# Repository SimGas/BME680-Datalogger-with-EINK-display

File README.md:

# BME680-Datalogger-with-EINK-display
Datalogger with BME680-Sensor, EINK Display, RTC and µSD-Storage

This project features a Arduino based datalogger reading temperature, relative humidity, pressure and IAQ values from a Bosch BME680 sensor. It displays the data at a 2.9 inch waveshare e-ink display using olikraus's u8g2 lib. The data is being synchronized with a DS3231 RTC and stored at a micro SD-Card.

The whole system runs on a adafruit feather M0 board

Please consider that this project is in a very early development status. I haven't completed the program code yet and I've just ordered the Mainboard.
If you want to make your own copy of this project, please contact me for information about recent unpublished changes.

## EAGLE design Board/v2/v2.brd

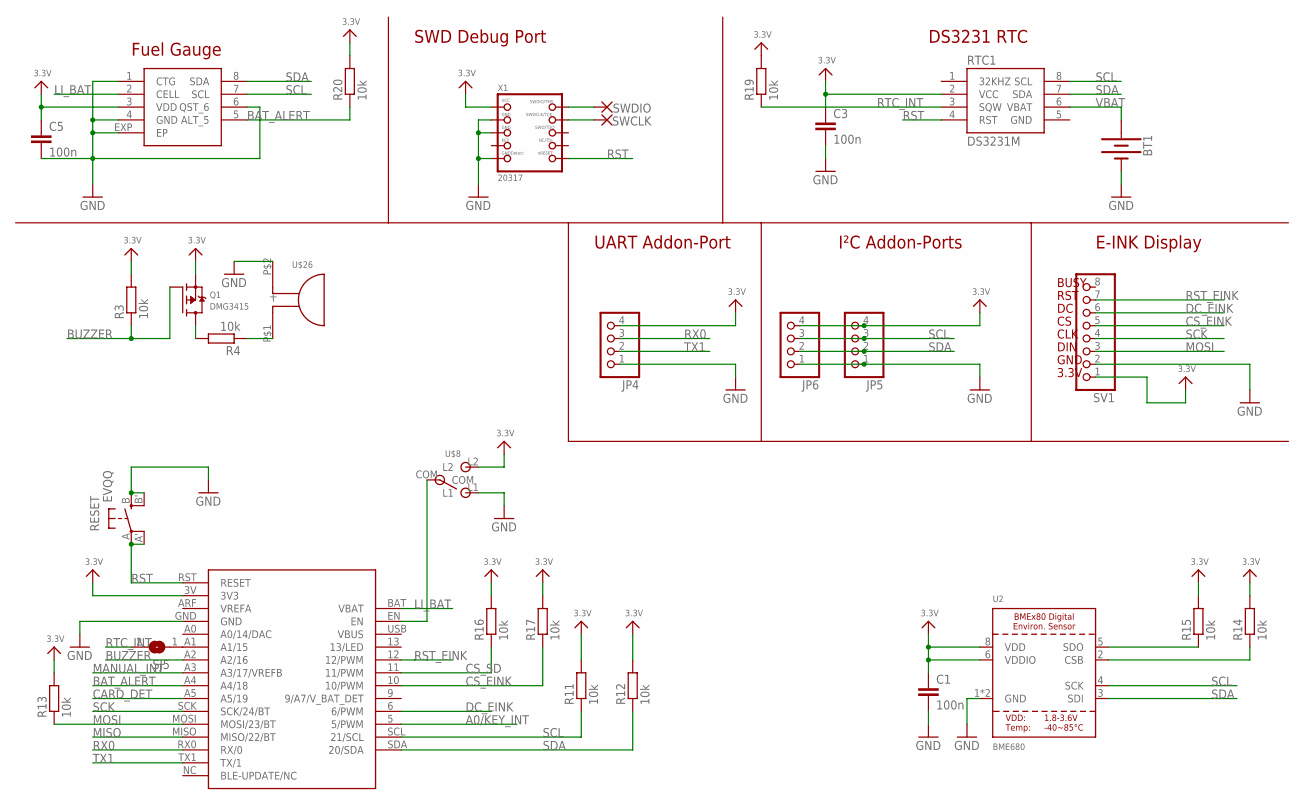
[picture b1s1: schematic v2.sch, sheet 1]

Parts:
BT1: BATTERY-12MM_SMD; BATTCON_12MM
C1, C3, C5: 100n; C0805
JP4, JP5, JP6: PINHD-1X04_2.54; 1X04
Q1: DMG3415; SOT23-WIDE
R3, R4, R11, R12, R13, R14, R15, R16, R17, R19, R20: 10k; R0805
RESET: EVQQ; EVQ-Q2
RTC1: DS3231M; SO08
SJ5: SOLDERJUMPERCLOSED; SOLDERJUMPER_CLOSEDWIRE
SV1: PINHD-1X08_2.54; 1X08
SWCLK: SMD1,27-2,54
SWDIO: SMD1,27-2,54
U2: BME680; BME280
U$8: MSK-12C02_SMD_SPDT_SWITCH; MSK-12C02
U$15: FEATHER_M0
U$26: DTS402G1; DET402G1
U$33: MAX17043; DFN-2X3
X1: 20317; 2X05_1.27MM_BOX_POSTS

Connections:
3.3V: C1.1, C3.1, C5.1, JP4.4, JP5.4, JP6.4, Q1.2 (S), R3.2, R11.2, R12.2, R13.2, R14.2, R15.2, R16.2, R17.2, R19.2, R20.2, RTC1.2 (VCC), SV1.1, U2.6 (VDDIO), U2.8 (VDD), U$8.L2, U$15.3V (3V3), U$33.3 (VDD), X1.1 (VCC); also elsewhere on the board
A0/KEY_INT: U$15.5 (5/PWM); also elsewhere on the board
BAT_ALERT: R20.1, U$15.A4 (A4/18), U$33.5 (ALT_5)
BUZZER: Q1.1 (G), R3.1, U$15.A2 (A2/16)
CARD_DET: U$15.A5 (A5/19); also elsewhere on the board
CS_EINK: R17.1, SV1.5, U$15.10 (10/PWM)
CS_SD: R16.1, U$15.11 (11/PWM); also elsewhere on the board
DC_EINK: SV1.6, U$15.6 (6/PWM)
EN: U$8.COM, U$15.EN
GND: BT1.GND (-), C1.2, C3.2, C5.2, JP4.1, JP5.1, JP6.1, RESET.B (S), RESET.B' (S1), RTC1.5 (GND), SV1.2, U2.1 (GND), U2.7 (GND), U$8.L1, U$15.GND, U$26.P$2 (-), U$33.1 (CTG), U$33.4 (GND), U$33.6 (QST_6), U$33.EXP (EP), X1.3 (GND), X1.5 (GND), X1.9 (GNDDETECT); also elsewhere on the board
LI_BAT: U$15.BAT (VBAT), U$33.2 (CELL)
MANUAL_INT: U$15.A3 (A3/17/VREFB); also elsewhere on the board
MISO: U$15.MISO (MISO/22/BT); also elsewhere on the board
MOSI: R13.1, SV1.3, U$15.MOSI (MOSI/23/BT); also elsewhere on the board
unnamed: R14.1, U2.2 (CSB)
unnamed: SJ5.1, U$15.A1 (A1/15)
unnamed: Q1.3 (D), R4.2
unnamed: R4.1, U$26.P$1 (+)
unnamed: R15.1, U2.5 (SDO)
unnamed: SWDIO.1, X1.2 (SWDIO)
unnamed: SWCLK.1, X1.4 (SWDCLK)
RST: RESET.A, RESET.A' (P1), RTC1.4 (RST), U$15.RST (RESET), X1.10 (NRESET)
RST_EINK: SV1.7, U$15.12 (12/PWM)
RTC_INT: R19.1, RTC1.3 (SQW), SJ5.2
RX0: JP4.3, U$15.RX0 (RX/0)
SCK: SV1.4, U$15.SCK (SCK/24/BT); also elsewhere on the board
SCL: JP5.3, JP6.3, R11.1, RTC1.8 (SCL), U2.4 (SCK), U$15.SCL (21/SCL), U$33.7 (SCL); also elsewhere on the board
SDA: JP5.2, JP6.2, R12.1, RTC1.7 (SDA), U2.3 (SDI), U$15.SDA (20/SDA), U$33.8 (SDA); also elsewhere on the board
TX1: JP4.2, U$15.TX1 (TX/1)
VBAT: BT1.PWR@1 (+), RTC1.6 (VBAT)

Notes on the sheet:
3.3V
GND
DIN
CLK
RST
BUSY
Fuel Gauge
SWD Debug Port
DS3231 RTC
E-INK Display
I²C Addon-Ports
UART Addon-Port

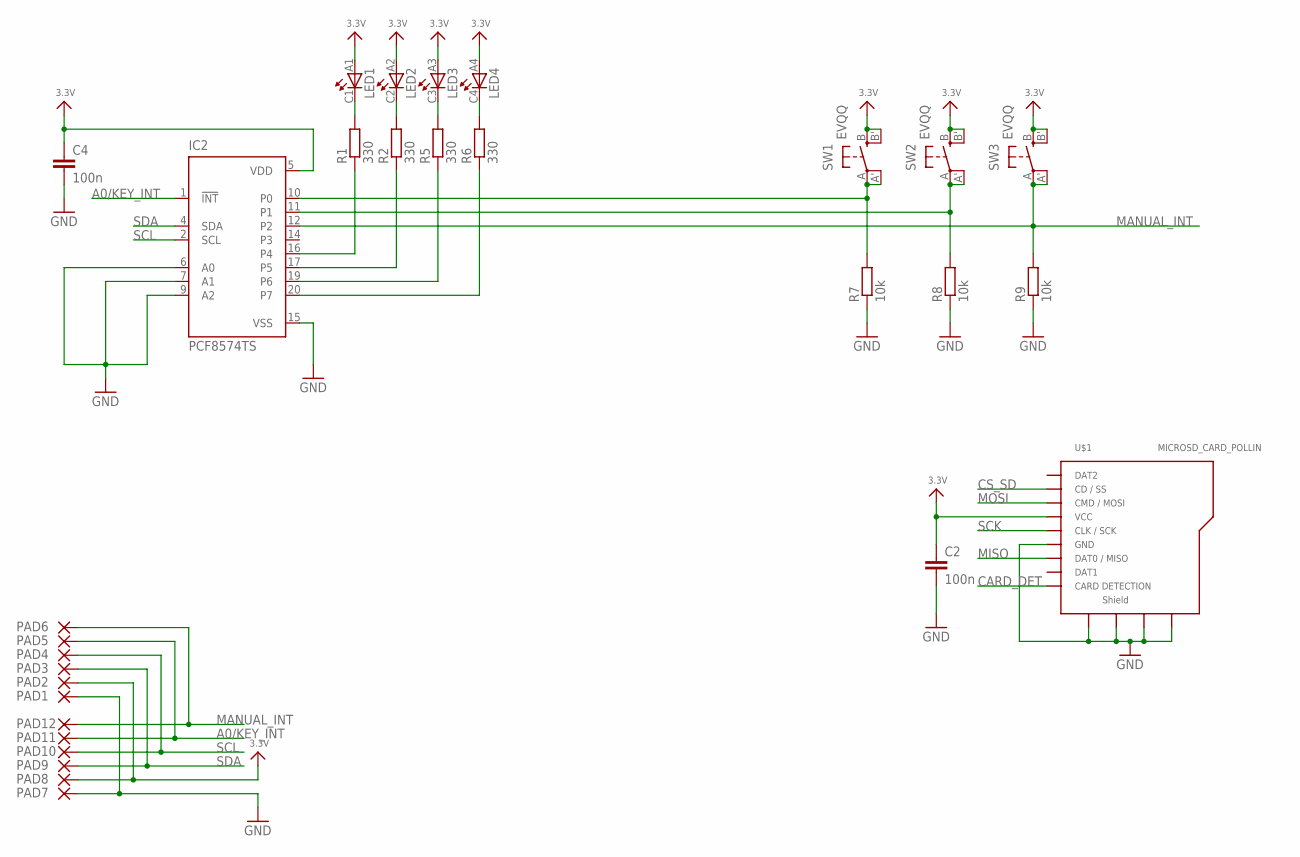
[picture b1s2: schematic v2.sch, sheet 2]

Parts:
C2, C4: 100n; C0805
IC2: PCF8574TS; SSOP20
PAD1, PAD2, PAD3, PAD4, PAD5, PAD6, PAD7, PAD8, PAD9, PAD10, PAD11, PAD12: SMD1,27-2,54
R1, R2, R5, R6: 330; R0805
R7, R8, R9: 10k; R0805
SW1, SW2, SW3: EVQQ; EVQ-Q2
U$1: MICROSD_CARD_POLLIN; MR**-AP*03**
U$5: LED_LIGHTGUIDE; LPA-C041301S-X

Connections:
3.3V: C2.1, C4.1, IC2.5 (VDD), PAD2.1, PAD8.1, SW1.B (S), SW1.B' (S1), SW2.B (S), SW2.B' (S1), SW3.B (S), SW3.B' (S1), U$1.VCC, U$5.A1, U$5.A2, U$5.A3, U$5.A4; also elsewhere on the board
A0/KEY_INT: IC2.1 (!INT), PAD5.1, PAD11.1; also elsewhere on the board
CARD_DET: U$1.CARD_DETECTION (CARD_D); also elsewhere on the board
CS_SD: U$1.DAT3/CS (CD/SS); also elsewhere on the board
GND: C2.2, C4.2, IC2.6 (A0), IC2.7 (A1), IC2.9 (A2), IC2.15 (VSS), PAD1.1, PAD7.1, R7.1, R8.1, R9.1, U$1.GND, U$1.SHD_1 (SHD1), U$1.SHD_2 (SHD2), U$1.SHD_3 (SHD3), U$1.SHD_4 (SHD4); also elsewhere on the board
MANUAL_INT: IC2.12 (P2), PAD6.1, PAD12.1, R9.2, SW3.A, SW3.A' (P1); also elsewhere on the board
MISO: U$1.DAT0 (DAT0/MISO); also elsewhere on the board
MOSI: U$1.CMD (CMD/MOSI); also elsewhere on the board
unnamed: IC2.16 (P4), R1.1
unnamed: IC2.17 (P5), R2.1
unnamed: IC2.10 (P0), R7.2, SW1.A, SW1.A' (P1)
unnamed: IC2.11 (P1), R8.2, SW2.A, SW2.A' (P1)
unnamed: IC2.19 (P6), R5.1
unnamed: IC2.20 (P7), R6.1
unnamed: R6.2, U$5.C4
unnamed: R5.2, U$5.C3
unnamed: R2.2, U$5.C2
unnamed: R1.2, U$5.C1
SCK: U$1.CLK (CLK/SCK); also elsewhere on the board
SCL: IC2.2 (SCL), PAD4.1, PAD10.1; also elsewhere on the board
SDA: IC2.4 (SDA), PAD3.1, PAD9.1; also elsewhere on the board

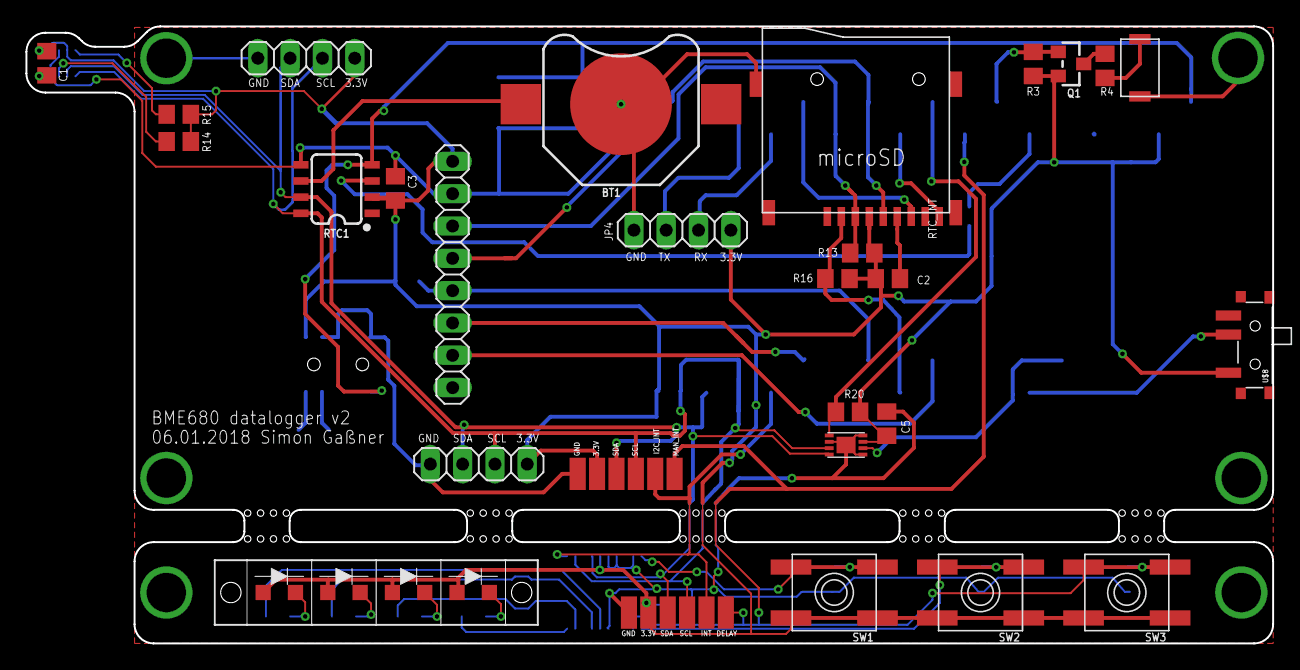
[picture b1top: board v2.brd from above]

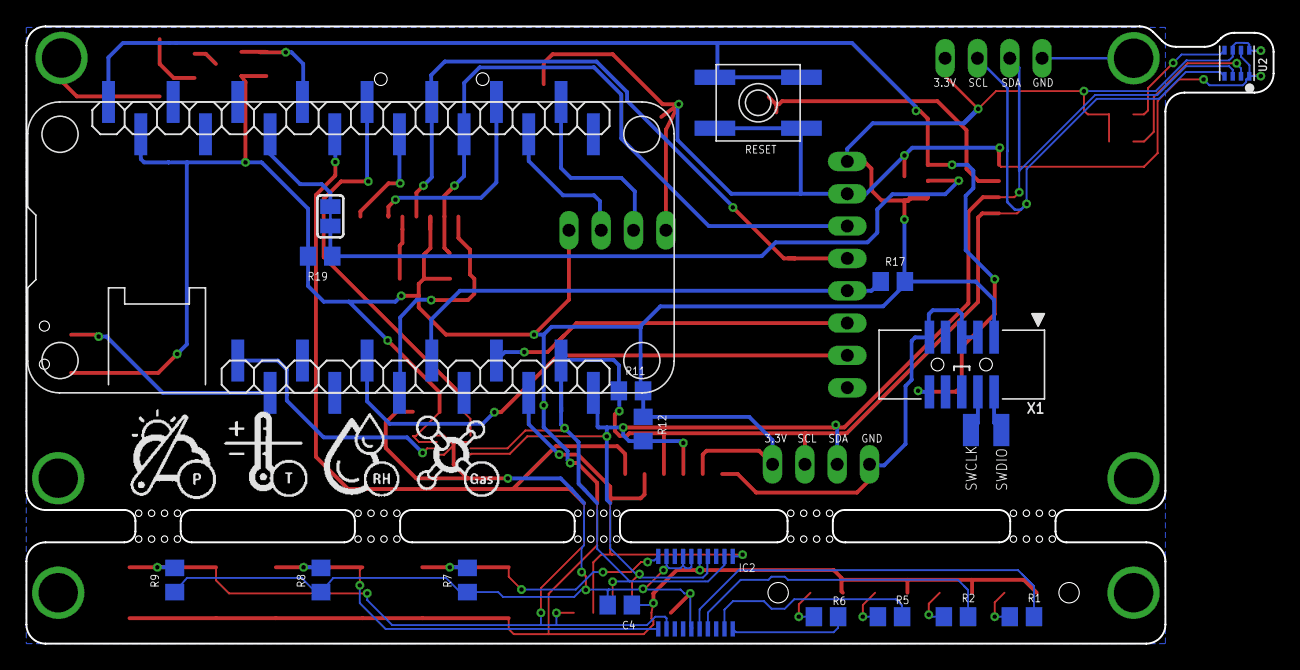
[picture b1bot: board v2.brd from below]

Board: 2 copper layers, 98.0 x 48.5 mm, 59 parts (20 on the bottom side), 40 nets.

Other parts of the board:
U$14: GASLOGO45MM; BME680_LOGO_30MM

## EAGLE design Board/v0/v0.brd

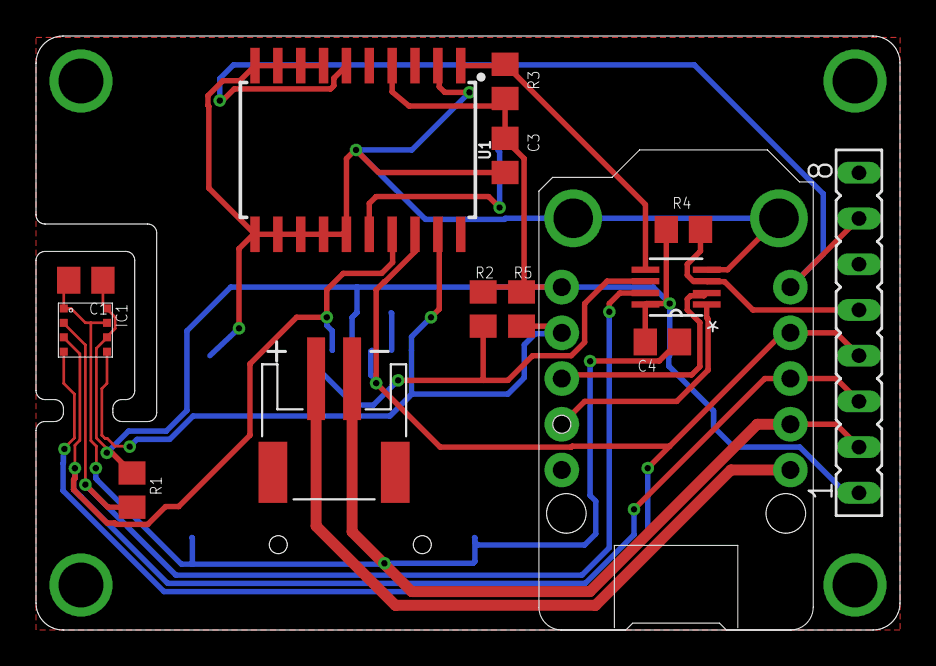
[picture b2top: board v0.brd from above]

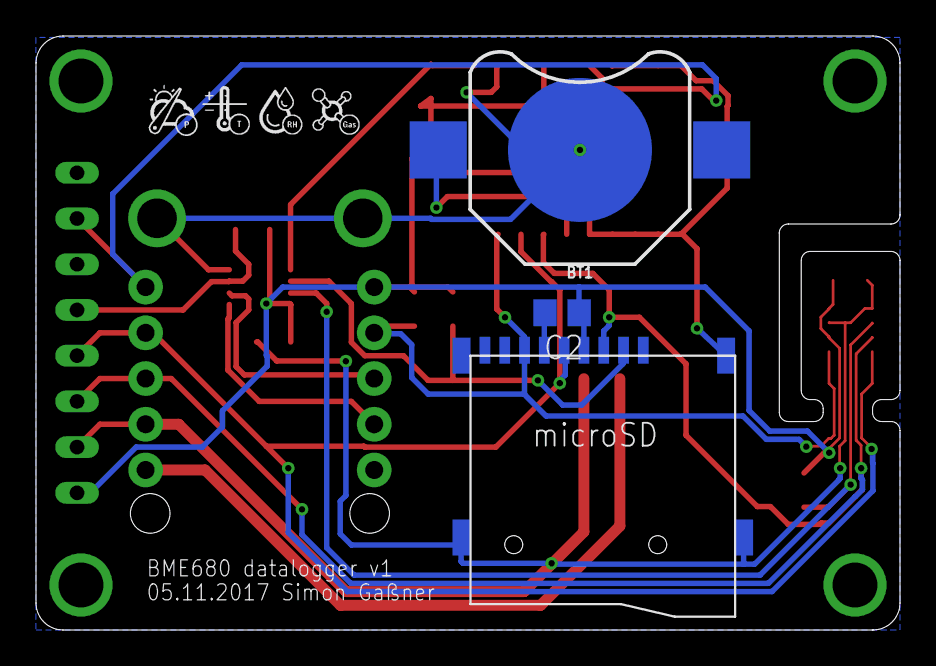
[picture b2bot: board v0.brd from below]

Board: 2 copper layers, 48.0 x 33.0 mm, 18 parts (4 on the bottom side), 14 nets.

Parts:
BT1: BATTCON_12MM
C1, C2, C3, C4: 100n; C0805
CN1: JST-PH-2-SMT-RA
IC1: BME680
R1, R2, R3, R4, R5: 10k; R0805
SV1: FE08
U1: DS3234; SO20-0.3
U2: SN74LVC1G139DCTR; SOP65P400X130-8N
U$1: MICROSD_CARD_POLLIN; MR**-AP*03**
U$8: TRINKET_M0
U$14: BME680_LOGO

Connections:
3.3V: C1.1, C2.1, C3.1, C4.1, IC1.6, IC1.8, R1.2, R2.2, R3.2, R4.2, R5.2, SV1.1, U1.4, U2.8, U$1.VCC, U$8.6
CS0: IC1.2, R1.1, U2.7
CS1: R2.1, U2.6, U$1.DAT3/CS
CS2: R3.1, U1.1, U2.5
CS3: R4.1, SV1.5, U2.3
CSD0: U2.1, U$8.9
CSD1: U2.2, U$8.8
GND: BT1.GND, C1.2, C2.2, C3.2, C4.2, CN1.2, IC1.1, IC1.7, SV1.2, U1.2, U1.7, U1.8, U1.9, U1.10, U1.11, U1.12, U1.13, U1.14, U1.15, U2.4, U$1.GND, U$1.SHD_1, U$1.SHD_2, U$1.SHD_3, U$1.SHD_4, U$8.2, U$8.11, U$8.12
MISO: IC1.5, R5.1, U1.19, U$1.DAT0, U$8.7
MOSI: IC1.3, SV1.3, U1.17, U$1.CMD, U$8.3
unnamed: BT1.PWR@1, U1.16
RST: SV1.7, U1.6, U$8.5
SCK: IC1.4, SV1.4, U1.18, U$1.CLK, U$8.4
V_BAT: CN1.1, U$8.1

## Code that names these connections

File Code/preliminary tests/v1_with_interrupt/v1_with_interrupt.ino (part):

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#include <Adafruit_BME280.h>
#include "RTClib.h"
//#define U8G2_16BIT
#define RST_EINK 12
#define DC_EINK 6
#define CS_EINK 10 
#define CS_SD 11
#define VBATPIN 9
#define RTC_INT 15 // For Arduino Zero, Pin number is required, not interrupt number 
#define SD_CardDetect 19

bool color = 1; //color switch. 1= black on white, 0 = white on black
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

delay(3000); // wait for console opening
   pinMode(RTC_INT, INPUT_PULLUP);
  attachInterrupt(digitalPinToInterrupt(RTC_INT), ISR, FALLING);  // Attach interrupt to pin 6 with an ISR and when the pin state CHANGEs

  SYSCTRL->XOSC32K.reg |=  (SYSCTRL_XOSC32K_RUNSTDBY | SYSCTRL_XOSC32K_ONDEMAND); // set external 32k oscillator to run when idle or sleep mode is chosen
  REG_GCLK_CLKCTRL  |= GCLK_CLKCTRL_ID(GCM_EIC) |  // generic clock multiplexer id for the external interrupt controller
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
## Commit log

2017-12-01 Intial Upload
2017-12-01 deleted some cloud conflict files
2017-12-02 Optimization
    Optimization of readability
    Exchange of Strings with sprintf command
    reduced spi writing speed
2017-12-03 Implementing Sleep Mode
    I finally got the Sleep Mode (IDLE2) running on the Feather M0.
    I had to use a workaround for the __WFI instruction as I don't know how to mask EIC's yet.
2017-12-03 Sleep Mode Test Example
2018-02-08 Updating Board
    New version of board with several changes and new CCS811 sensor

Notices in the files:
parts and their libraries:
SparkFun-Batteries: Licensing: Creative Commons ShareAlike 4.0 International - https://creativecommons.org/licenses/by-sa/4.0
microbuilder: This work is placed in the public domain, and may be freely used for commercial and non-commercial work with the following conditions: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
